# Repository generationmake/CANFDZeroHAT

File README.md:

# CANFDZeroHAT
Raspberry Pi HAT with Microchip MCP2517FD or MCP2518FD CAN FD controller

The board uses a 40 MHz crystal. This is the default crystal for the linux module. The first prototypes used a 20 MHz crystal.

The controller can be connected to SPI0 CE0 or CE1 by populating different resistor jumpers. Also different GPIOs can be used as interrupt.

## setup

edit `/boot/config.txt` and add line:

`dtoverlay=mcp251xfd,spi0-0,interrupt=25`

If you use a crystal different to 40 MHz you have to specify the frequency:

`dtoverlay=mcp251xfd,spi0-0,oscillator=20000000,interrupt=25`

keep care that you choose the right interrupt and SPI CE line and populate the corresponding resistor.

enable CAN after boot up with

`sudo ip link set can0 up type can bitrate 250000`

## connectors

### CAN connector CN2

Terminal block with 3.81 mm grid.

| **Pin** | **Signal**    | **Description**                  |
|:-------:|:-------------:|:--------------------------------:|
| 1       | GND           |                                  |
| 2       | CAN_L         |                                  |
| 3       | CAN_H         |                                  |
| 4       | VCC           | up to 5.5 V                      |

### UAVCAN dronecode connector CN3 and CN4

compatible to UAVCAN dronecode. JST GH 1.25mm 4-pin.

| **Pin** | **Signal**    | **Description**                  |
|:-------:|:-------------:|:--------------------------------:|
| 1       | CANVCC        | up to 5.5 V                      |
| 2       | CAN_H         |                                  |
| 3       | CAN_L         |                                  |
| 4       | GND           |                                  |

CANVCC can be connected to the Raspberry Pi via diode D1 as desribed in the dronecode spec. The direction of the diode defines wether current is sourced from the connector or supplied into the UAVCAN system. If no connection is desired just leave D1 unpopulated.

## PCB

### Top

### Bottom

## Resources

### Datasheets

 * http://ww1.microchip.com/downloads/en/DeviceDoc/MCP2517FD-External-CAN-FD-Controller-with-SPI-Interface-20005688B.pdf
 * https://ww1.microchip.com/downloads/en/DeviceDoc/External-CAN-FD-Controller-with-SPI-Interface-DS20006027B.pdf

## License

This hardware is licensed under the CERN OHL v. 1.2

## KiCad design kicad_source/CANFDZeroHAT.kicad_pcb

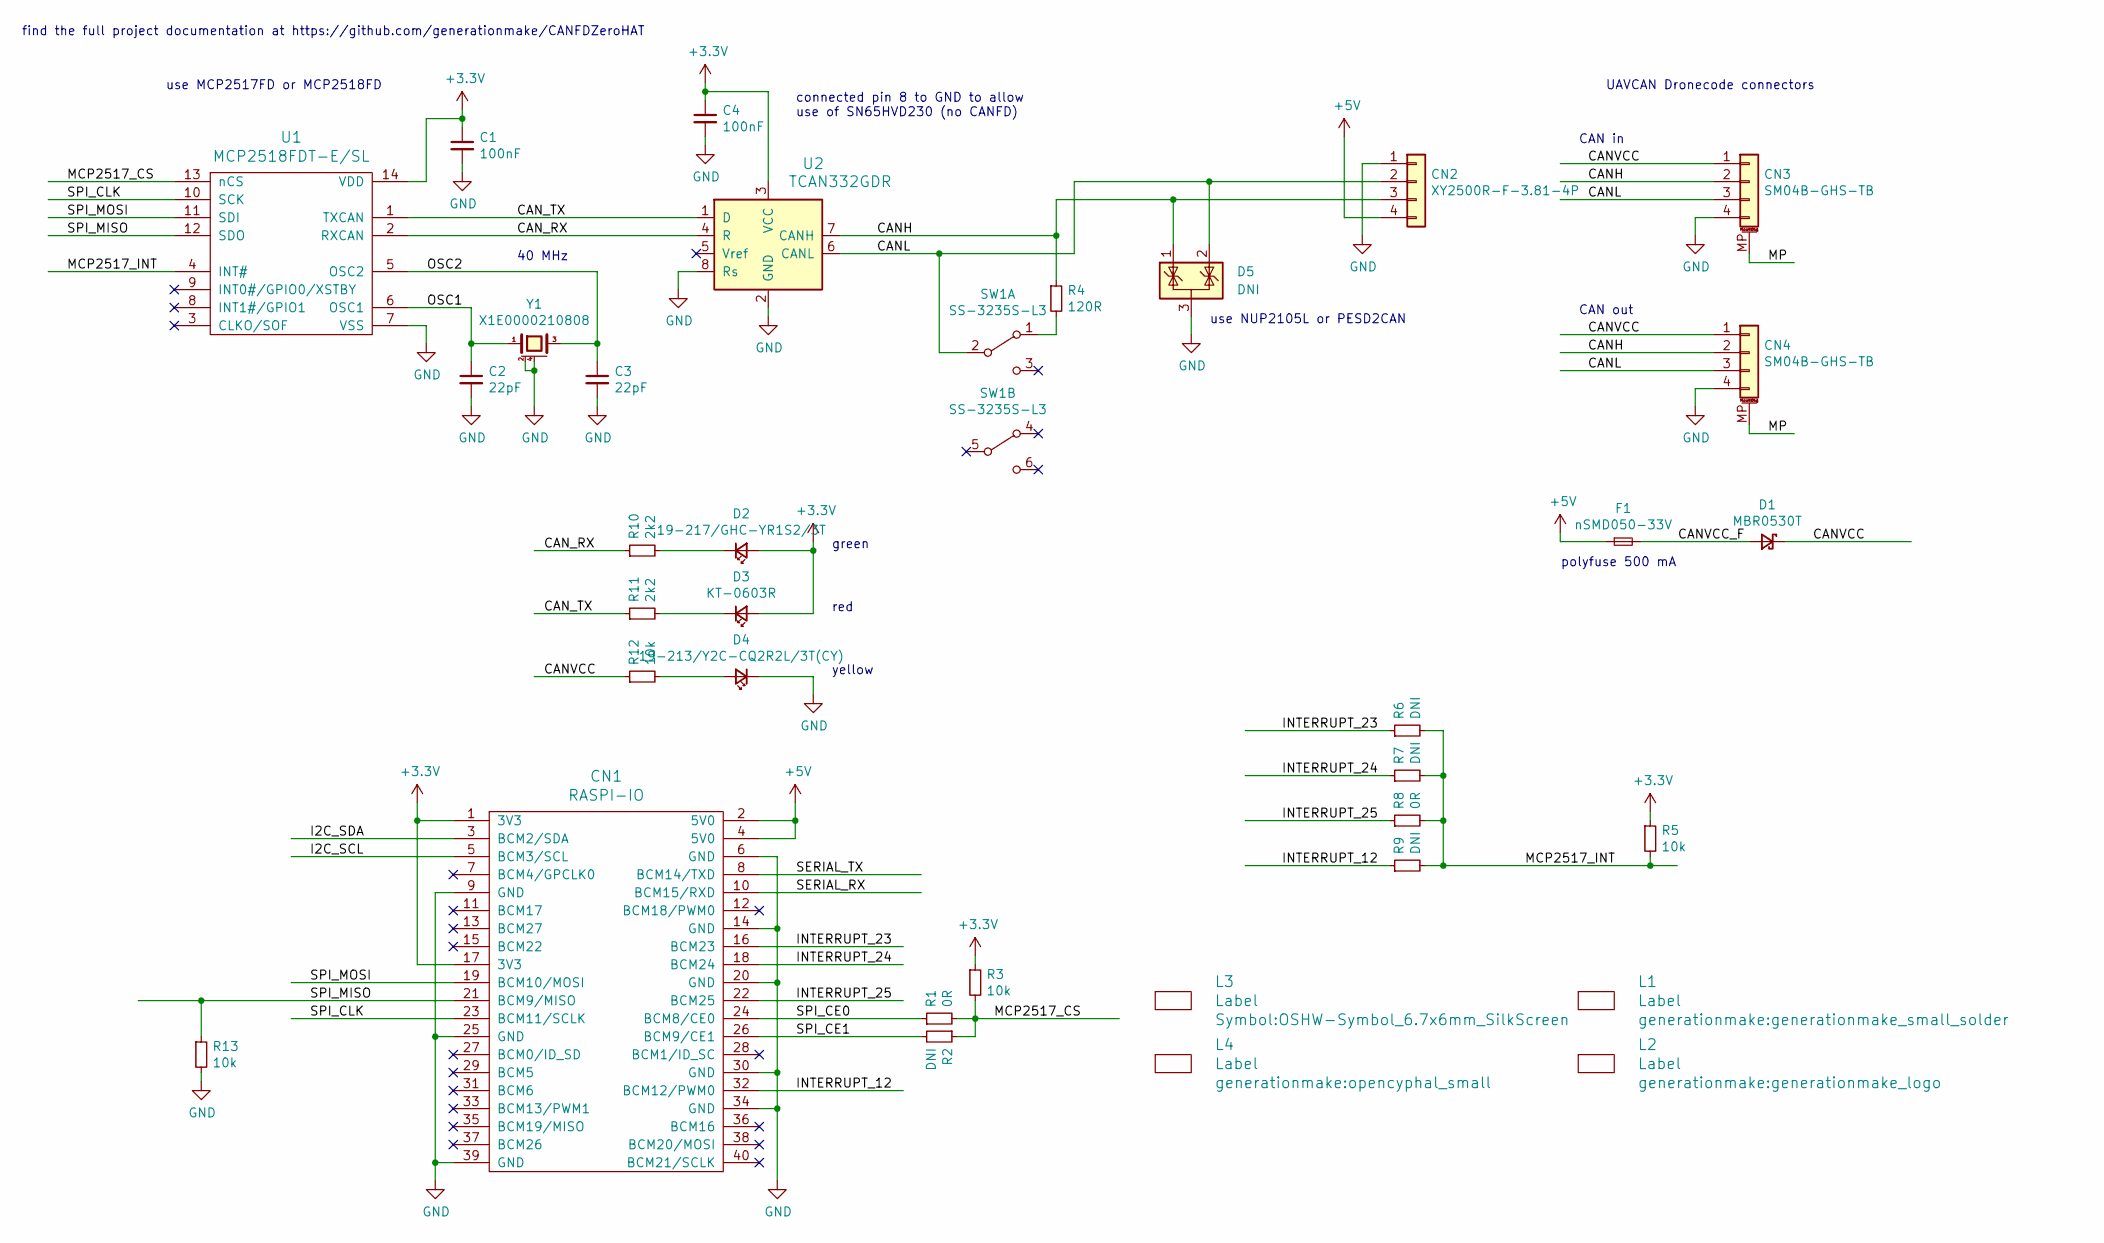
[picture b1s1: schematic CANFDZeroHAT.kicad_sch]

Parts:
C1, C4: 100nF; C_0603_1608Metric; LCSC C14663
C2, C3: 22pF; C_0603_1608Metric
CN1: RASPI-IO; RASPI_ZERO_HAT_EDGE; LCSC C50982
CN2: XY2500R-F-3.81-4P; PhoenixContact_MC_1,5_4-G-3.81_1x04_P3.81mm_Horizontal; LCSC C880583
CN3, CN4: SM04B-GHS-TB; JST_GH_SM04B-GHS-TB_1x04-1MP_P1.25mm_Horizontal; LCSC C189895
D1: MBR0530T; D_SOD-123; LCSC C77336
D2: 19-217/GHC-YR1S2/3T; LED_0603_1608Metric; LCSC C72043
D3: KT-0603R; LED_0603_1608Metric; LCSC C2286
D4: 19-213/Y2C-CQ2R2L/3T(CY); LED_0603_1608Metric; LCSC C72038
D5: DNI; SOT-23
F1: nSMD050-33V; Fuse_1206_3216Metric; LCSC C70077
L1: Label; generationmake_small_solder
L2: Label; generationmake_logo
L3: Label; OSHW-Symbol_6.7x6mm_SilkScreen
L4: Label; opencyphal_small
R1, R8: 0R; R_0603_1608Metric; LCSC C2889381
R2, R6, R7, R9: DNI; R_0603_1608Metric
R3, R5, R12, R13: 10k; R_0603_1608Metric; LCSC C25804
R4: 120R; R_0603_1608Metric; LCSC C22787
R10, R11: 2k2; R_0603_1608Metric; LCSC C4190
SW1: SS-3235S-L3; SW_DPDT_XKB_SS-3235S-L3; LCSC C381098
U1: MCP2518FDT-E/SL; SOIC-14_3.9x8.7mm_P1.27mm; LCSC C626758
U2: TCAN332GDR; SOIC-8_3.9x4.9mm_P1.27mm; LCSC C191010
Y1: X1E0000210808; Crystal_SMD_3225-4Pin_3.2x2.5mm; LCSC C255941

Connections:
+3.3V: C1.1, C4.1, CN1.1 (3V3), CN1.17 (3V3), D2.2 (A), D3.2 (A), R3.1, R5.1, U1.14 (VDD), U2.3 (VCC)
+5V: CN1.2 (5V0), CN1.4 (5V0), CN2.4, F1.1
/CANH: CN2.3, CN3.2, CN4.2, D5.1 (K), R4.1, U2.7 (CANH)
/CANL: CN2.2, CN3.3, CN4.3, D5.2 (K), SW1.2 (B), U2.6 (CANL)
/CANVCC: CN3.1, CN4.1, D1.1 (K), R12.1
/CANVCC_F: D1.2 (A), F1.2
/CAN_RX: R10.1, U1.2 (RXCAN), U2.4 (R)
/CAN_TX: R11.1, U1.1 (TXCAN), U2.1 (D)
/I2C_SCL: CN1.5 (BCM3/SCL)
/I2C_SDA: CN1.3 (BCM2/SDA)
/INTERRUPT_12: CN1.32 (BCM12/PWM0), R9.1
/INTERRUPT_23: CN1.16 (BCM23), R6.1
/INTERRUPT_24: CN1.18 (BCM24), R7.1
/INTERRUPT_25: CN1.22 (BCM25), R8.1
/MCP2517_CS: R1.2, R2.1, R3.2, U1.13 (nCS)
/MCP2517_INT: R5.2, R6.2, R7.2, R8.2, R9.2, U1.4 (INT#)
/MP: CN3.MP (MountPin), CN4.MP (MountPin)
/OSC1: C2.1, U1.6 (OSC1), Y1.1
/OSC2: C3.1, U1.5 (OSC2), Y1.3
/SERIAL_RX: CN1.10 (BCM15/RXD)
/SERIAL_TX: CN1.8 (BCM14/TXD)
/SPI_CE0: CN1.24 (BCM8/CE0), R1.1
/SPI_CE1: CN1.26 (BCM9/CE1), R2.2
/SPI_CLK: CN1.23 (BCM11/SCLK), U1.10 (SCK)
/SPI_MISO: CN1.21 (BCM9/MISO), R13.1, U1.12 (SDO)
/SPI_MOSI: CN1.19 (BCM10/MOSI), U1.11 (SDI)
GND: C1.2, C2.2, C3.2, C4.2, CN1.6 (GND), CN1.9 (GND), CN1.14 (GND), CN1.20 (GND), CN1.25 (GND), CN1.30 (GND), CN1.34 (GND), CN1.39 (GND), CN2.1, CN3.4, CN4.4, D4.1 (K), D5.3 (A), R13.2, U1.7 (VSS), U2.2 (GND), U2.8 (Rs), Y1.2 (case), Y1.4 (case)
unnamed: D2.1 (K), R10.2
unnamed: D3.1 (K), R11.2
unnamed: D4.2 (A), R12.2
unnamed: R4.2, SW1.1 (A)

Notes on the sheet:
green
find the full project documentation at https://github.com/generationmake/CANFDZeroHAT
CAN in
CAN out
UAVCAN Dronecode connectors
use NUP2105L or PESD2CAN
connected pin 8 to GND to allow use of SN65HVD230 (no CANFD)
red
40 MHz
yellow
polyfuse 500 mA
use MCP2517FD or MCP2518FD

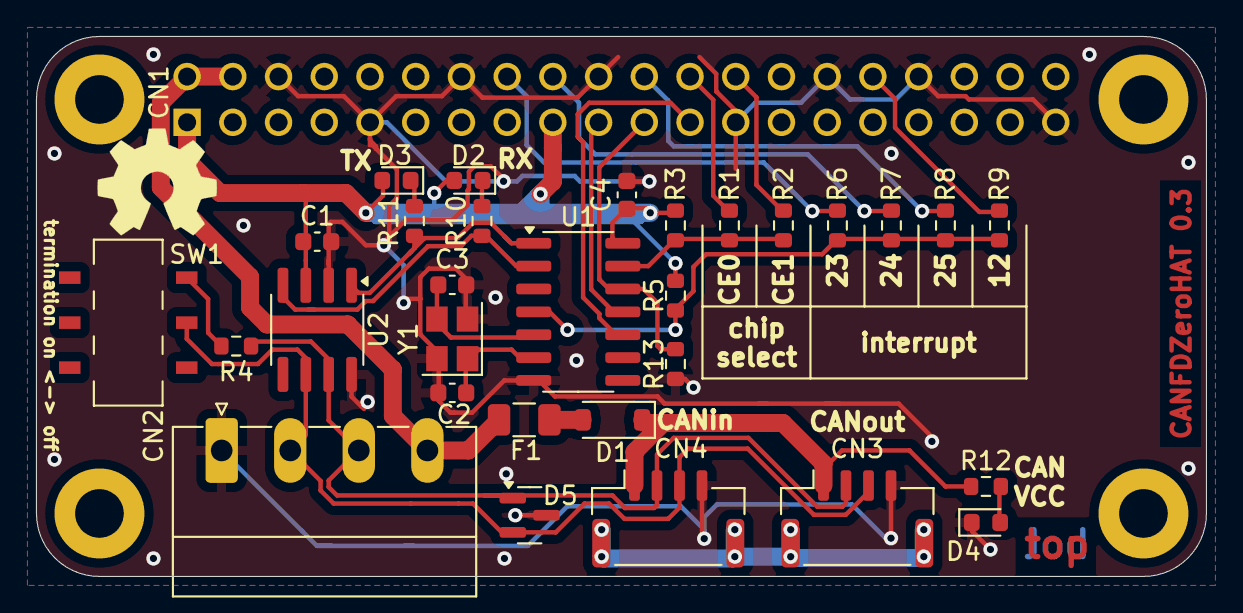
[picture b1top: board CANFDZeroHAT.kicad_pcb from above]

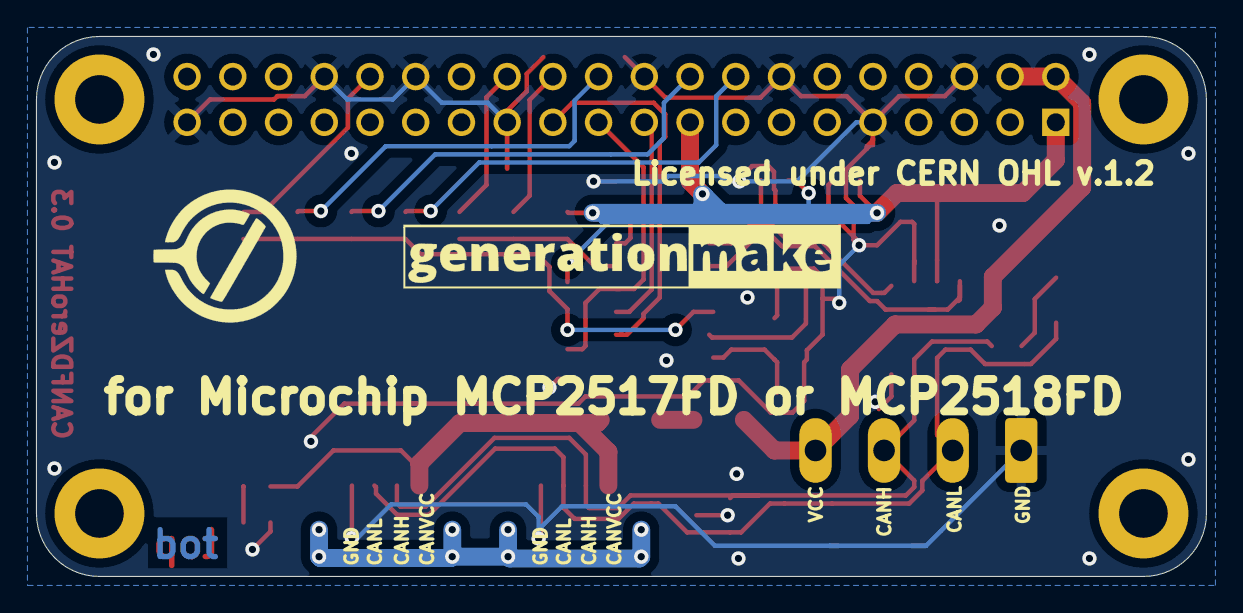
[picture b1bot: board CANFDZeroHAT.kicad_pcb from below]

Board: 2 copper layers, 65.0 x 30.0 mm, 35 parts (2 on the bottom side), 27 nets.

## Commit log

2020-12-13 added project from template
2020-12-13 generated schematic and layout
2020-12-18 added option resistors, updated layout
2020-12-18 updated some part numbers
2020-12-20 added pdf schematic
2020-12-20 added images, updated readme
2021-01-02 updated schematic, added fuse and debug leds
2021-01-02 updated layout
2021-01-08 added information on setup to readme
2021-01-24 added license cern OHL
2021-01-25 corrected footprint of CAN transceiver
2021-01-25 updated 40 MHz crystal
2021-01-26 made debug leds low active
2021-01-26 updated labels
2021-01-26 updated schematic pdf and images
2021-01-26 added 3d model of board
2021-01-31 added information on crystal frequency
2021-01-31 corrected typo
2023-08-24 updated project to KiCAD 6
2023-08-24 added mounting pad on CAN connector
2023-08-24 updated footprints, added pulldown on SDO
2023-08-24 updated symbol of CAN driver
2023-08-24 added protection on CAN, updated schematic pdf
2023-08-26 added some JLCPCB part numbers
2023-08-26 added cyphal logo
2025-02-23 added one JLCPCB part number
2025-02-23 updated to KiCAD 8
2025-02-23 removed unnecesary files
2025-02-23 fixed lirary errors and DRCs
2025-02-23 updated step file

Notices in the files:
kicad_source/CANFDZeroHAT.kicad_pcb:
Licensed under CERN OHL v.1.2
